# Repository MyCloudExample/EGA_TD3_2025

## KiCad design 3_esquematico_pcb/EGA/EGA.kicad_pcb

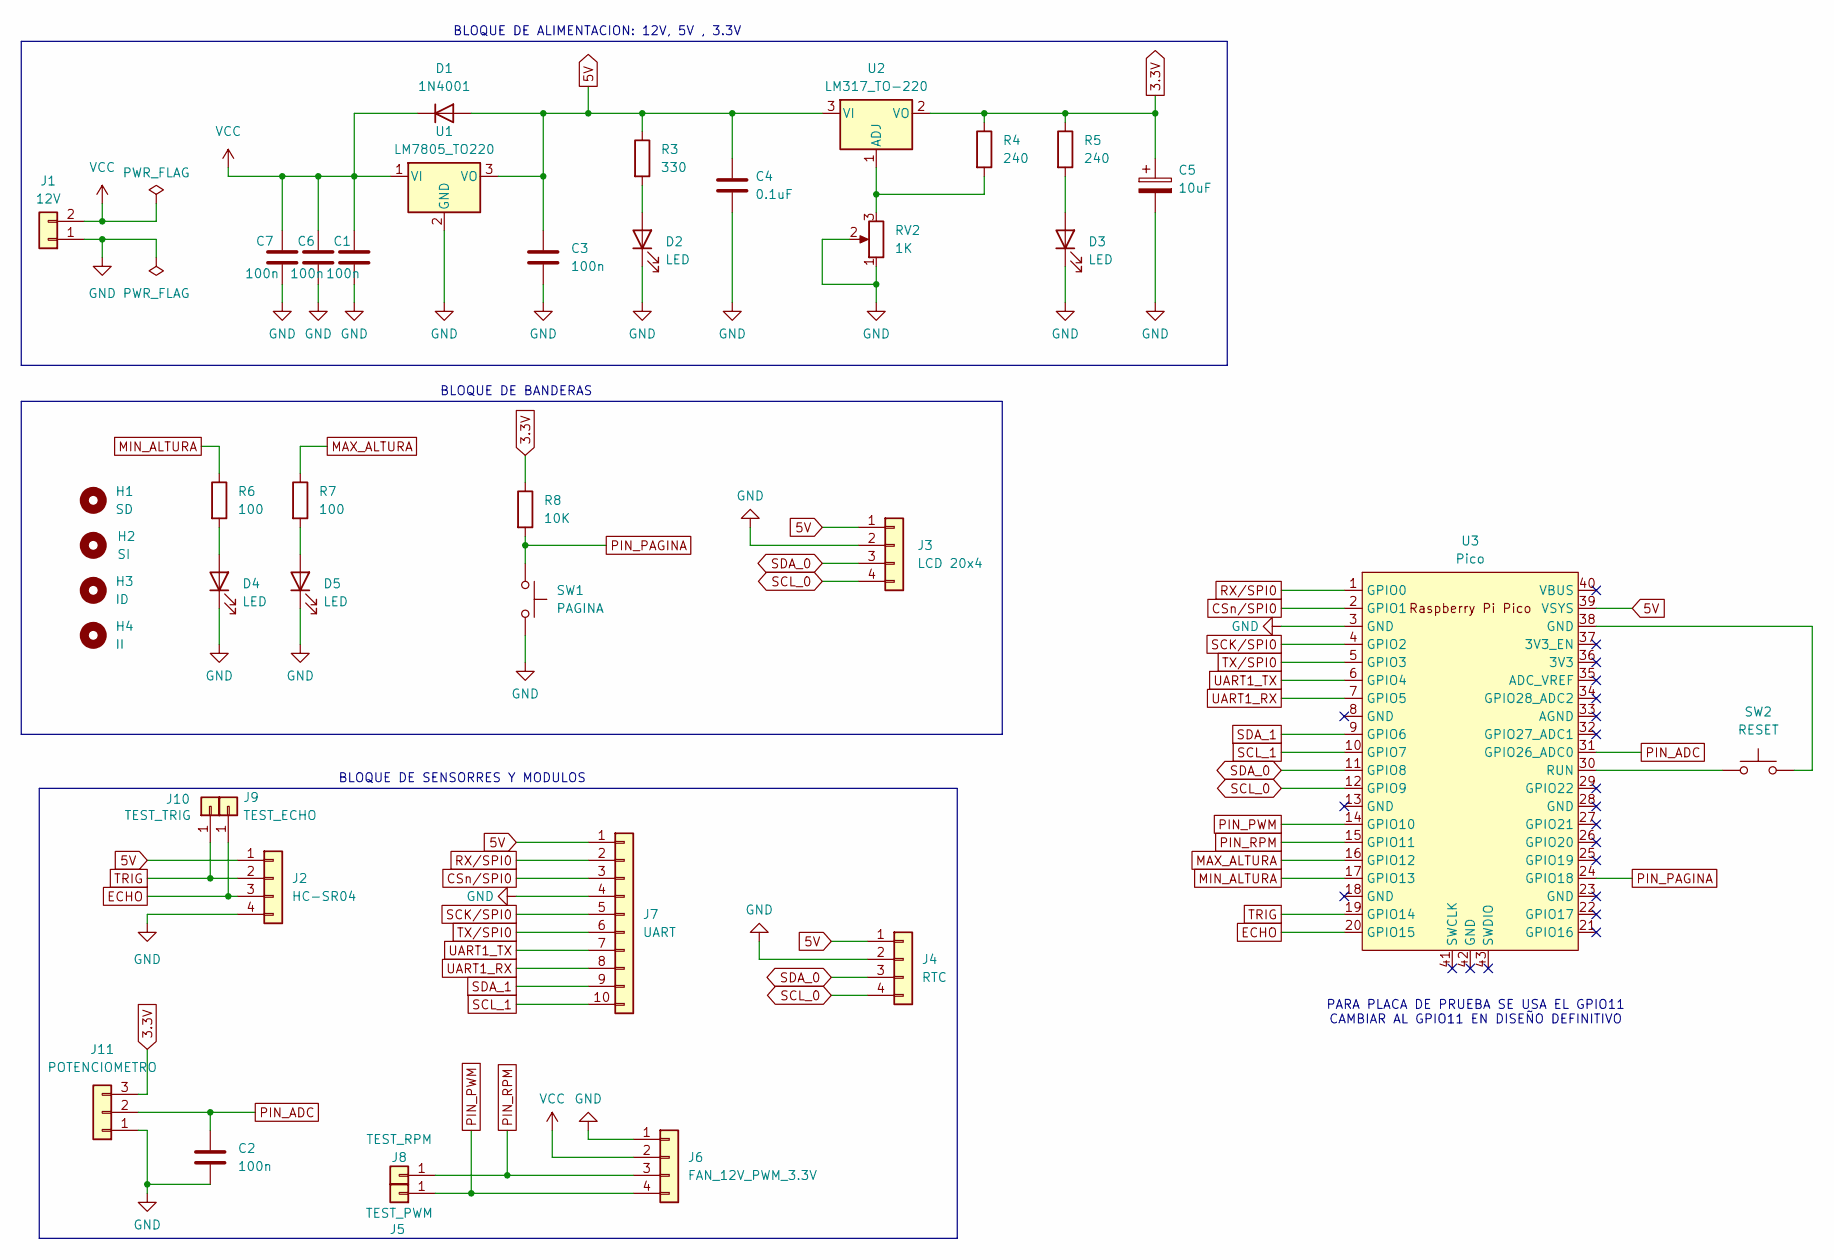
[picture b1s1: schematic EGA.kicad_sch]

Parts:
C1, C2, C3, C6, C7: 100n; C_Disc_D5.0mm_W2.5mm_P2.50mm
C4: 0.1uF; C_Disc_D5.0mm_W2.5mm_P2.50mm
C5: 10uF; CP_Radial_D5.0mm_P2.50mm
D1: 1N4001; D_DO-41_SOD81_P10.16mm_Horizontal
D2, D3, D4, D5: LED; LED_D5.0mm
H1: SD; MountingHole_2.1mm
H2: SI; MountingHole_2.1mm
H3: ID; MountingHole_2.1mm
H4: II; MountingHole_2.1mm
J1: 12V; Molex_KK-254_AE-6410-02A_1x02_P2.54mm_Vertical
J2: HC-SR04; PinHeader_1x04_P2.54mm_Vertical
J3: LCD 20x4; PinHeader_1x04_P2.54mm_Vertical
J4: RTC; PinHeader_1x04_P2.54mm_Vertical
J5: TEST_PWM; PinHeader_1x01_P2.54mm_Vertical
J6: FAN_12V_PWM_3.3V; PinHeader_1x04_P2.54mm_Vertical
J7: UART; PinHeader_1x10_P2.54mm_Vertical
J8: TEST_RPM; PinHeader_1x01_P2.54mm_Vertical
J9: TEST_ECHO; PinHeader_1x01_P2.54mm_Vertical
J10: TEST_TRIG; PinHeader_1x01_P2.54mm_Vertical
J11: POTENCIOMETRO; PinHeader_1x03_P2.54mm_Vertical
R3: 330; R_Axial_DIN0204_L3.6mm_D1.6mm_P7.62mm_Horizontal
R4, R5: 240; R_Axial_DIN0204_L3.6mm_D1.6mm_P7.62mm_Horizontal
R6, R7: 100; R_Axial_DIN0204_L3.6mm_D1.6mm_P7.62mm_Horizontal
R8: 10K; R_Axial_DIN0204_L3.6mm_D1.6mm_P7.62mm_Horizontal
RV2: 1K; Potentiometer_Vishay_T93YA_Vertical
SW1: PAGINA; SW_PUSH_6mm_H8mm
SW2: RESET; SW_PUSH_6mm_H8mm
U1: LM7805_TO220; TO-220-3_Vertical
U2: LM317_TO-220; TO-220-3_Vertical
U3: Pico; RPi_Pico_SMD_TH

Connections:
3.3V: C5.1, J11.3, R4.1, R5.1, R8.1, U2.2 (VO)
5V: C3.1, C4.1, D1.2 (A), J2.1, J3.1, J4.1, J7.1, R3.1, U1.3 (VO), U2.3 (VI), U3.39 (VSYS)
CSn/SPI0: J7.3, U3.2 (GPIO1)
ECHO: J2.3, J9.1, U3.20 (GPIO15)
GND: C1.2, C2.2, C3.2, C4.2, C5.2, C6.2, C7.2, D2.1 (K), D3.1 (K), D4.1 (K), D5.1 (K), J1.1, J2.4, J3.2, J4.2, J6.1, J7.4, J11.1, RV2.1, RV2.2, SW1.2, U1.2 (GND), U3.3 (GND)
MAX_ALTURA: R7.1, U3.16 (GPIO12)
MIN_ALTURA: R6.1, U3.17 (GPIO13)
unnamed: D2.2 (A), R3.2
unnamed: D3.2 (A), R5.2
unnamed: D4.2 (A), R6.2
unnamed: D5.2 (A), R7.2
unnamed: SW2.2, U3.38 (GND)
unnamed: R4.2, RV2.3, U2.1 (ADJ)
unnamed: SW2.1, U3.30 (RUN)
PIN_ADC: C2.1, J11.2, U3.31 (GPIO26_ADC0)
PIN_PAGINA: R8.2, SW1.1, U3.24 (GPIO18)
PIN_PWM: J5.1, J6.4, U3.14 (GPIO10)
PIN_RPM: J6.3, J8.1, U3.15 (GPIO11)
RX/SPI0: J7.2, U3.1 (GPIO0)
SCK/SPI0: J7.5, U3.4 (GPIO2)
SCL_0: J3.4, J4.4, U3.12 (GPIO9)
SCL_1: J7.10, U3.10 (GPIO7)
SDA_0: J3.3, J4.3, U3.11 (GPIO8)
SDA_1: J7.9, U3.9 (GPIO6)
TRIG: J2.2, J10.1, U3.19 (GPIO14)
TX/SPI0: J7.6, U3.5 (GPIO3)
UART1_RX: J7.8, U3.7 (GPIO5)
UART1_TX: J7.7, U3.6 (GPIO4)
VCC: C1.1, C6.1, C7.1, D1.1 (K), J1.2, J6.2, U1.1 (VI)

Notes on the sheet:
PARA PLACA DE PRUEBA SE USA EL GPIO11 CAMBIAR AL GPIO11 EN DISEÑO DEFINITIVO
BLOQUE DE ALIMENTACION: 12V, 5V , 3.3V
BLOQUE DE SENSORRES Y MODULOS
BLOQUE DE BANDERAS

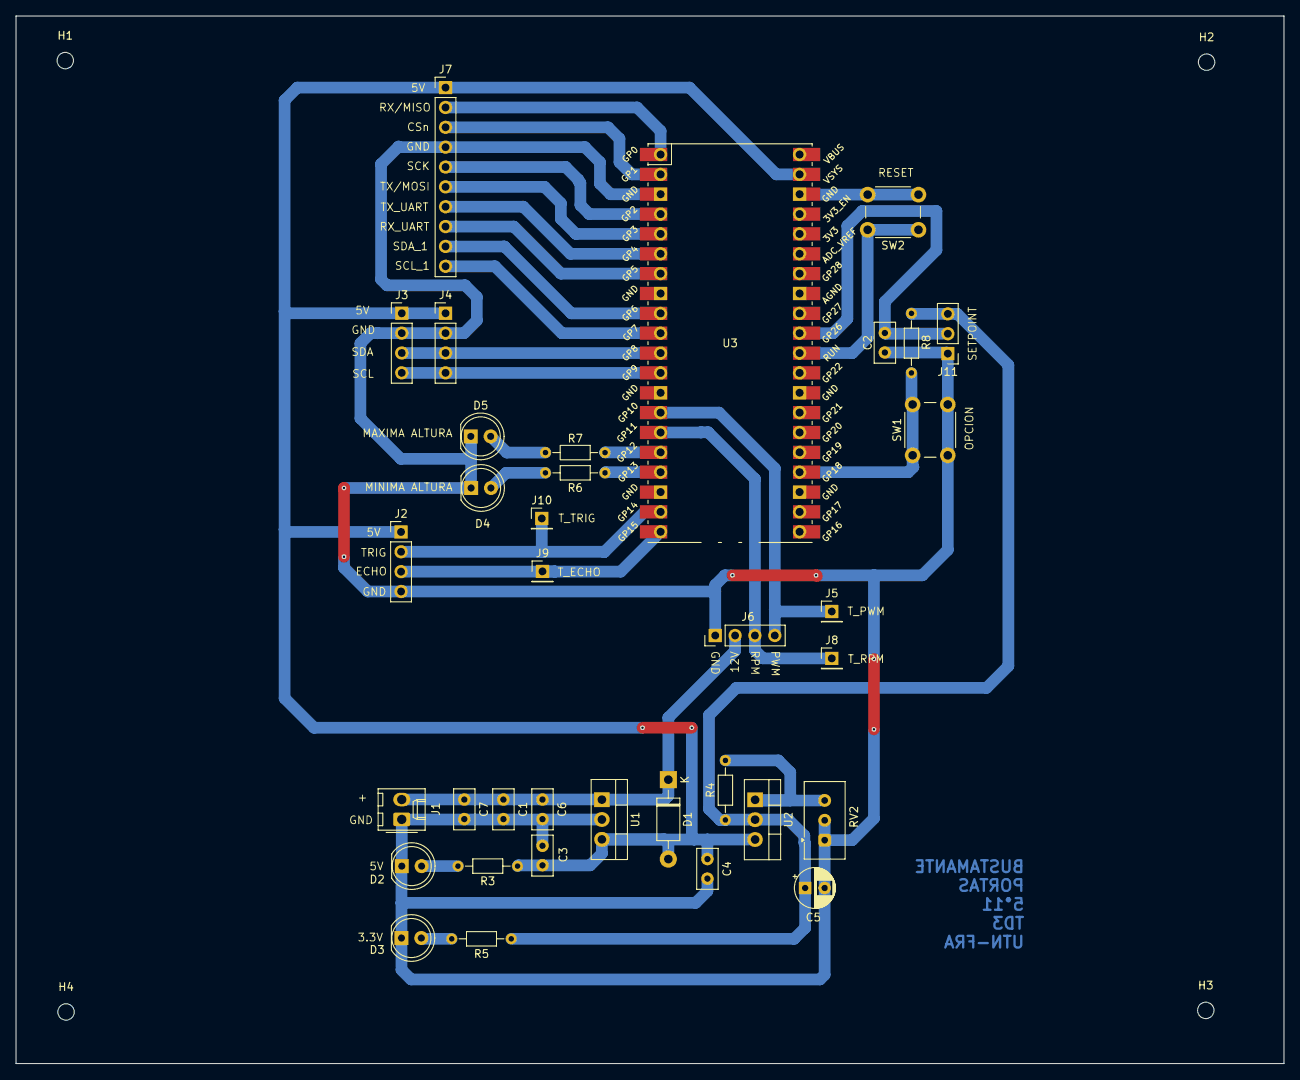
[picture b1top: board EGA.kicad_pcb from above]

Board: 2 copper layers, 162.2 x 134.0 mm, 39 parts (0 on the bottom side), 29 nets.

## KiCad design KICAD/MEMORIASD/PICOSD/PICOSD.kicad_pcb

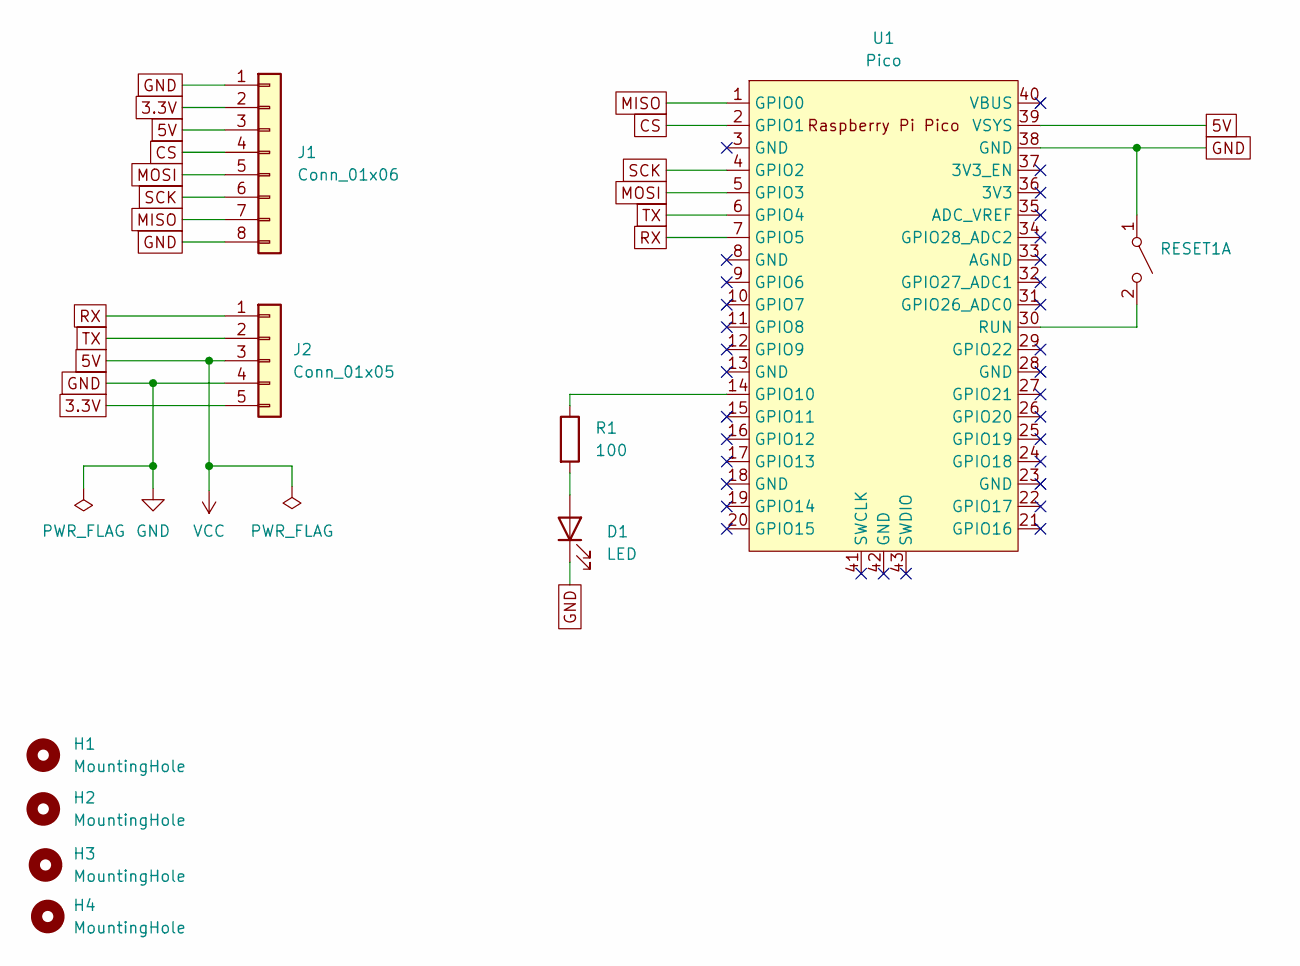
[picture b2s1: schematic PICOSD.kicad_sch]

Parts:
D1: LED; LED_D5.0mm
H1, H2, H3, H4: MountingHole; MountingHole_4mm
J1: Conn_01x06; PinHeader_1x08_P2.54mm_Vertical
J2: Conn_01x05; PinHeader_1x05_P2.54mm_Vertical
R1: 100; R_Axial_DIN0204_L3.6mm_D1.6mm_P7.62mm_Horizontal
RESET1: SW_DPST_x2; SW_Push_2P1T_Toggle_CK_PVA1xxH4xxxxxxV2
U1: Pico; RPi_Pico_SMD_TH

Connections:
3.3V: J1.2, J2.5
5V: J1.3, J2.3, U1.39 (VSYS)
CS: J1.4, U1.2 (GPIO1)
GND: D1.1 (K), J1.1, J1.8, J2.4, RESET1.1 (A), U1.38 (GND)
MISO: J1.7, U1.1 (GPIO0)
MOSI: J1.5, U1.5 (GPIO3)
unnamed: D1.2 (A), R1.2
unnamed: RESET1.2 (B), U1.30 (RUN)
unnamed: R1.1, U1.14 (GPIO10)
RX: J2.1, U1.7 (GPIO5)
SCK: J1.6, U1.4 (GPIO2)
TX: J2.2, U1.6 (GPIO4)

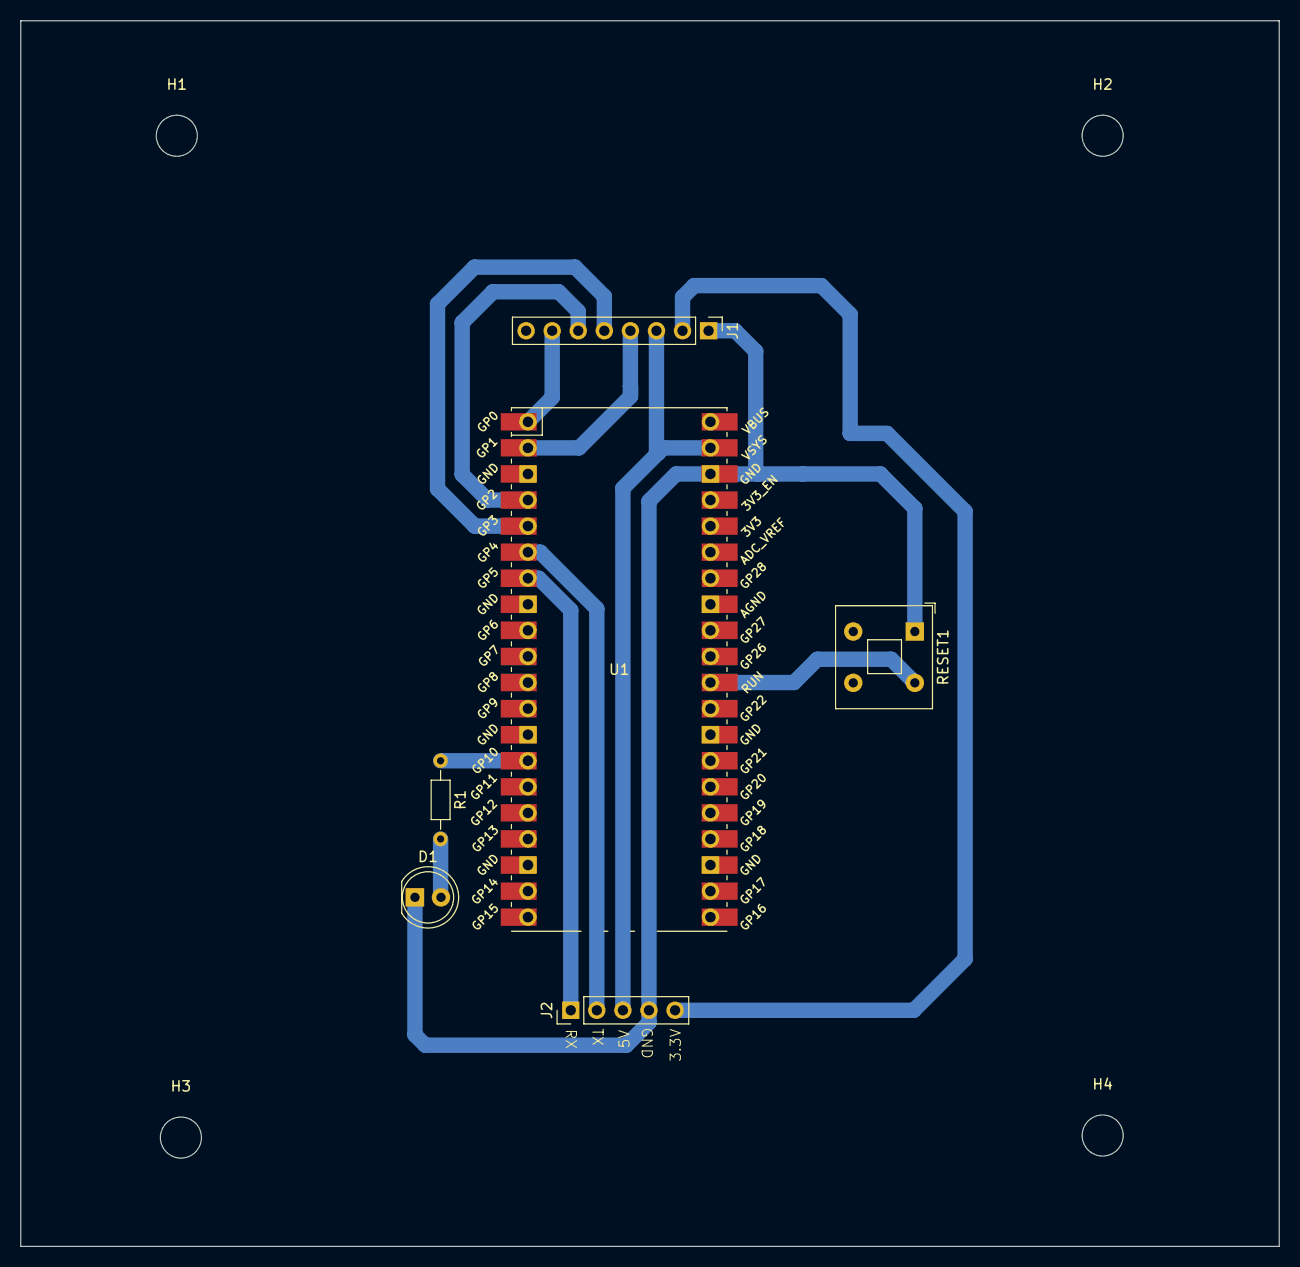
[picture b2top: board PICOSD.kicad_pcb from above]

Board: 2 copper layers, 122.6 x 119.4 mm, 10 parts (0 on the bottom side), 12 nets.

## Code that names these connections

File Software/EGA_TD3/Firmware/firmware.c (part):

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#define ADDR        0x27    //Direccion del LCD en I2C
#define FREQ        400000  //Frecuencia de 100KHz para el i2c
//========================================DEFINICION DE FAN=========================================================================
#define PIN_PWM     10      //Pin 21 de la placa 11
#define PIN_RPM     11      //Pin 22 de la placa 10
//NOTA EN LA PLACA DE PRUEBA SE USA EL PIN 11 PARA EL PWM, PERO EN LA PLACA PCB SE UTILIZA EL PIN 10, RECORDAR CAMBIARLO
//========================================PINES DE HC-SR04==========================================================================
#define PIN_TRIG    14      //Pin 19 de la placa
#define PIN_ECHO    15      //Pin 20 de la placa
//NOTA: PLaca de prueba se usa el GPIO 14 pata TRIG y GPIO 15 para ECHO
//========================================PIN DE POTENCIOMETRO PARA EL SETPOINT=====================================================
#define PIN_ADC     26      //Pin 31 de la placa
//=======================================PINES PARA EL SPI=========================================================================
/*#define PIN_TX  4           //Pin 6 de la placa
#define PIN_RX  5           //Pin 7 de la placa
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#define GPIO_LED_MIN 13     //Pin 17 de la placa
#define ALERTA_TIMEOUT_MS 3000//Tiempo de encendido, solo se uso para testeo
//=======================================BOTON SE SELECCION PARA LOS SETPOINT=======================================================
#define PIN_PAGINA  18      // Pin 24 de la placa
#define DEBOUNCE_TIME_MS 50//Tiempo para evitar rebotes
#define MULTI_PRESS_TIMEOUT 300//Tiempo para evitar rebotes
//========================================PARAMETROS FISICOS PARA EL CONTROL PID====================================================
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/*----------------------------------------------------------------------------------------------------------------------------------*/
/*----------------------------------------VARAIBLES DE RPOGRAMA, COLAS Y SEMAFOROS--------------------------------------------------*/
//========================================VARIABLES QUE NO SON PROPIAS DE FREERTOS==================================================
pwm_config_t cooler={.pin=PIN_PWM, .wrap=4999, .clk_div=1.0f};
hc_sr04_t sensor;
typedef struct
{
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void task_init(void *params) 
{
    // Inicializacion de GPIO para HC-SR04
    hc_sr04_init(&sensor,PIN_TRIG,PIN_ECHO);
    //Inicializacion del I2C
    i2c_init(I2C, FREQ);
    gpio_set_function(PIN_SDA, GPIO_FUNC_I2C);
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    gpio_pull_up(PIN_SCL);
    //Inicializo el ADC
    adc_init();
    adc_gpio_init(PIN_ADC);
    adc_select_input(0);
    //Inicializo el LCD
    lcd_init(I2C,ADDR);
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
void task_monitor_gpio(void *pvParameters) {
    while (1) {
        printf("Estado GPIO24: %d \n", gpio_get(PIN_PAGINA));
        vTaskDelay(pdMS_TO_TICKS(100));
       
    }
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
void configuracion_gpio_boton(void) {
    // Configuración del botón en GPIO 14
    gpio_init(PIN_PAGINA);
    gpio_set_dir(PIN_PAGINA, GPIO_IN);
    gpio_pull_up(PIN_PAGINA);   // configura pull down
    //gpio_set_irq_enabled_with_callback(PIN_PAGINA, GPIO_IRQ_EDGE_RISE, true, &boton_callback);   // cuando detecta evento, \
                                                                                            evento: GPIO_IRQ_EDGE_RISE (flanco ascendente), \
                                                                                            TRUE: habilita la interrupcion para este GPIO, \
                                                                                            va a la dirección de memoria en la que la función “boton_callback” se encuentra
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    printf("Despues de la cola Contador= %d\n",contador);
    while (1) 
    {
        bool current_state = gpio_get(PIN_PAGINA);
        if (current_state != last_state) 
        {
            last_debounce_time = xTaskGetTickCount();
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    //static uint16_t last_pwm = BASE_PWM;
   // 1. Verificación PWM
    pwm_config_t fan = {
        .pin = PIN_PWM,
        .wrap = 4999,
        .clk_div = 1.0f
    };
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
    // 2. Verificación sensor
    hc_sr04_t sensor;
    hc_sr04_init(&sensor, PIN_TRIG, PIN_ECHO);
    /*printf("\nPrueba del sensor:\n");
    for(int i = 0; i < 5; i++) {
        float dist = hc_sr04_get_distance_cm(&sensor);
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
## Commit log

2025-07-05 Carpeta de EGA, Esta fuera del repo de TD3, Usadp para subir y testear
2025-07-05 Subida de diseño en KICAD
2025-07-10 Agregado de lista de componentes con sus dimensiones, Tutorial de inclusion de libreria para simnolo y footprint
2025-07-14 Actualizacion KICAD 13/7/2025
2025-07-14 Adicion de COOLER_2
2025-07-15 Adicion de PCB_Preliminar para entregar en la segunda parte
2025-07-16 SD modulo añadido
2025-07-16 Carpeta para calibrar el PWM con la altura
2025-07-16 Adicion de testeo de memoria SD
2025-07-16 Actualizacion de titulo en lista de compoentes
2025-07-16 Eliminacion de gitignore en carperta Firmware
2025-07-17 Actualizacion de EGA en KICAD
2025-07-19 guardianas para lcd y sd
2025-07-19 Adicion de test para pulsador
2025-07-19 Actualizacion de compiacion de Firmware.c
2025-07-19 Funciona HC-SR04 con guardiana lcd
2025-07-19 Funcionamiento de setpoint, setpointmax y setpointmin
2025-07-23 task_gurdiana_leds funciona
2025-07-23 Adicion de PID en TEST_EGA, Libreria de PID
2025-07-26 task_rtc_funciona
2025-07-26 task_guradina_lcd_funciona_sensor_setpoint
2025-07-28 Actualizacion KICAD, CAmbio de pines en UART, los pines de I2C se mantienen sin cambios
2025-07-30 Cambios en Kicad, adicion de Cuentionario, Adicion de informe
2025-07-30 task_memoriSD funciona
2025-07-30 Actualizacion 30_7_2025
2025-07-31 Plano de masa en PCB
2025-08-02 Cuentionario, Adicion de palca para memoria SD
2025-08-02 Codigo bare metal PID, modificacion esquematico
2025-08-02 Actualizacion de build
2025-08-04 Actualizacion de informe, Adicion de EXAMPLE a PID, Lsita de componente
2025-08-04 Punto de partida para nueva rama
2025-08-09 Funcionamiento de PID con LCD, task_setpoint y medicion del sensor
2025-08-10 tarea task_guardiana_leds funciona
2025-08-10 Actualizacion de PCB de KICAD
2025-08-10 Paso previo a la rama de task_guardina_sd
2025-08-10 Funciona task_guradina_sd junto con las taras de PID, LCD, BOTON
2025-08-10 Adicion de presentacion con 3 segundos
2025-08-10 Version Final 1
2025-08-10 Actualizacion de Kicad, Adicion de manual de usuario
2025-08-12 Adicion en Informe, Adicion de Diagrama de tareas y conexiones, Ajuste de los K del PID, Adicion de modulo SD en KICAD
2025-08-12 Actualizacion de Kicad de la placa
2025-08-21 Actualizacion de informe
2025-08-23 features/Rama Agregado de SD
2025-08-23 Creacion de rama nueva
2025-08-23 Correccion de maximos y minimos , funciona
2025-08-26 Informe version 4
2025-08-26 Actualizacion de Firmware, mejora de comunicacion con PID
2025-08-28 Version de entrega V1
2025-12-01 Correcion de Informe
2025-12-01 Adicion de Explicacion del codigo de la EGA
2025-12-11 Actualizacion 10/12/2025
2025-12-11 Video de EGA
